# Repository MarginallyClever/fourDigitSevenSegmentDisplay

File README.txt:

Seven segment displays - practical examples.

Part 1 is a single Seven segment display connected to Arduino UNO.
Part 2 is two Seven segment displays connected to Arduino UNO via shift registers.

See https://www.marginallyclever.com/2017/02/shift-registers-and-seven-segment-displays-in-arduino
for the tutorial, discussion, and lots of other great stuff.

Please support our work: Like, share, and buy from marginallyclever.com today.  Thank you!

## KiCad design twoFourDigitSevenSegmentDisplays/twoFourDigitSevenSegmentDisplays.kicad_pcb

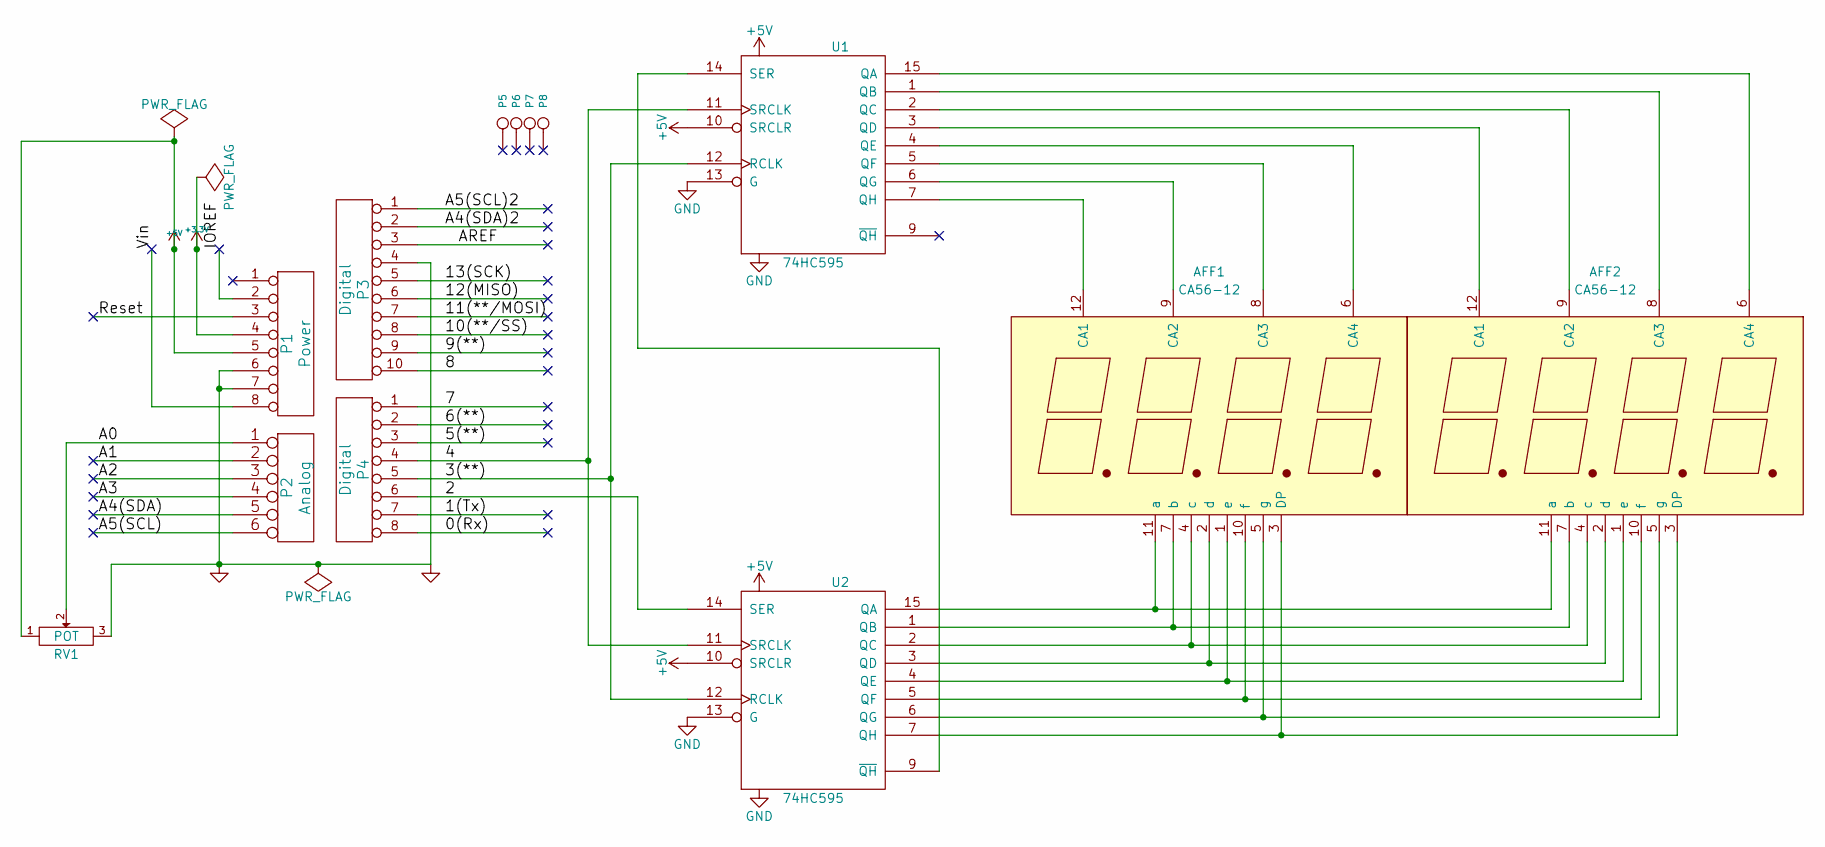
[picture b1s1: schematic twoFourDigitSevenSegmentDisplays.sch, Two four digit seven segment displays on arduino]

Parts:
AFF1, AFF2: CA56-12; Cx56-12
P1: Power; Socket_Strip_Arduino_1x08
P2: Analog; Socket_Strip_Arduino_1x06
P3: Digital; Socket_Strip_Arduino_1x10
P4: Digital; Socket_Strip_Arduino_1x08
P5, P6, P7, P8: CONN_1; Arduino_1pin
RV1: POT; Potentiometer_Piher_T16H_Single_Vertical
U1, U2: 74HC595; DIP-16_W7.62mm

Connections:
+3V3: P1.4
+5V: P1.5, RV1.1, U1.10 (SRCLR), U1.16 (VCC), U2.10 (SRCLR), U2.16 (VCC)
/0(Rx): P4.8
/1(Tx): P4.7
/2: P4.6, U2.14 (SER)
/3(**): P4.5, U1.12 (RCLK), U2.12 (RCLK)
/4: P4.4, U1.11 (SRCLK), U2.11 (SRCLK)
/5(**): P4.3
/6(**): P4.2
/7: P4.1
/8: P3.10
/9(**): P3.9
/10(**/SS): P3.8
/11(**/MOSI): P3.7
/12(MISO): P3.6
/13(SCK): P3.5
/A0: P2.1, RV1.2
/A1: P2.2
/A2: P2.3
/A3: P2.4
/A4(SDA): P2.5
/A4(SDA)2: P3.2
/A5(SCL): P2.6
/A5(SCL)2: P3.1
/AREF: P3.3
/IOREF: P1.2
/Reset: P1.3
/Vin: P1.8
GND: P1.6, P1.7, P3.4, RV1.3, U1.8 (GND), U1.13 (G), U2.8 (GND), U2.13 (G)
unnamed: AFF1.1 (e), AFF2.1 (e), U2.4 (QE)
unnamed: AFF1.2 (d), AFF2.2 (d), U2.3 (QD)
unnamed: AFF1.3 (DP), AFF2.3 (DP), U2.7 (QH)
unnamed: AFF1.4 (c), AFF2.4 (c), U2.2 (QC)
unnamed: AFF1.5 (g), AFF2.5 (g), U2.6 (QG)
unnamed: AFF1.6 (CA4), U1.4 (QE)
unnamed: AFF1.7 (b), AFF2.7 (b), U2.1 (QB)
unnamed: AFF1.8 (CA3), U1.5 (QF)
unnamed: AFF1.9 (CA2), U1.6 (QG)
unnamed: AFF1.10 (f), AFF2.10 (f), U2.5 (QF)
unnamed: AFF1.11 (a), AFF2.11 (a), U2.15 (QA)
unnamed: AFF1.12 (CA1), U1.7 (QH)
unnamed: AFF2.6 (CA4), U1.15 (QA)
unnamed: AFF2.8 (CA3), U1.1 (QB)
unnamed: AFF2.9 (CA2), U1.2 (QC)
unnamed: AFF2.12 (CA1), U1.3 (QD)
unnamed: U1.14 (SER), U2.9 (~QH)

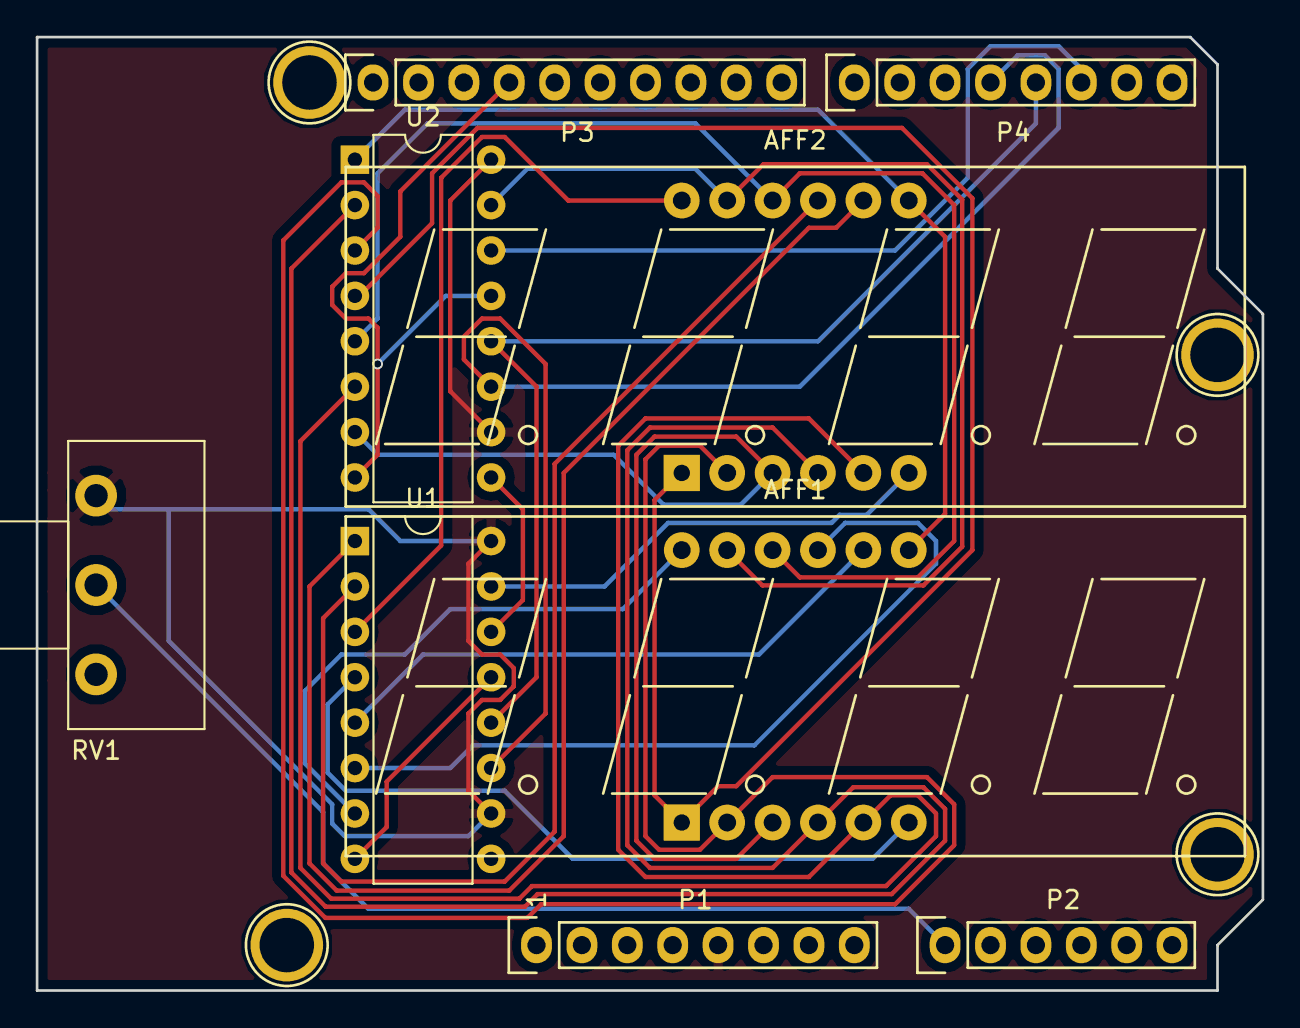
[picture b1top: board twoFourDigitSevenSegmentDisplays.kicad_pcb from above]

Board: 2 copper layers, 68.6 x 53.3 mm, 13 parts (0 on the bottom side), 23 nets.

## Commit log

2017-02-22 :confetti_ball: Added .gitattributes & .gitignore files
